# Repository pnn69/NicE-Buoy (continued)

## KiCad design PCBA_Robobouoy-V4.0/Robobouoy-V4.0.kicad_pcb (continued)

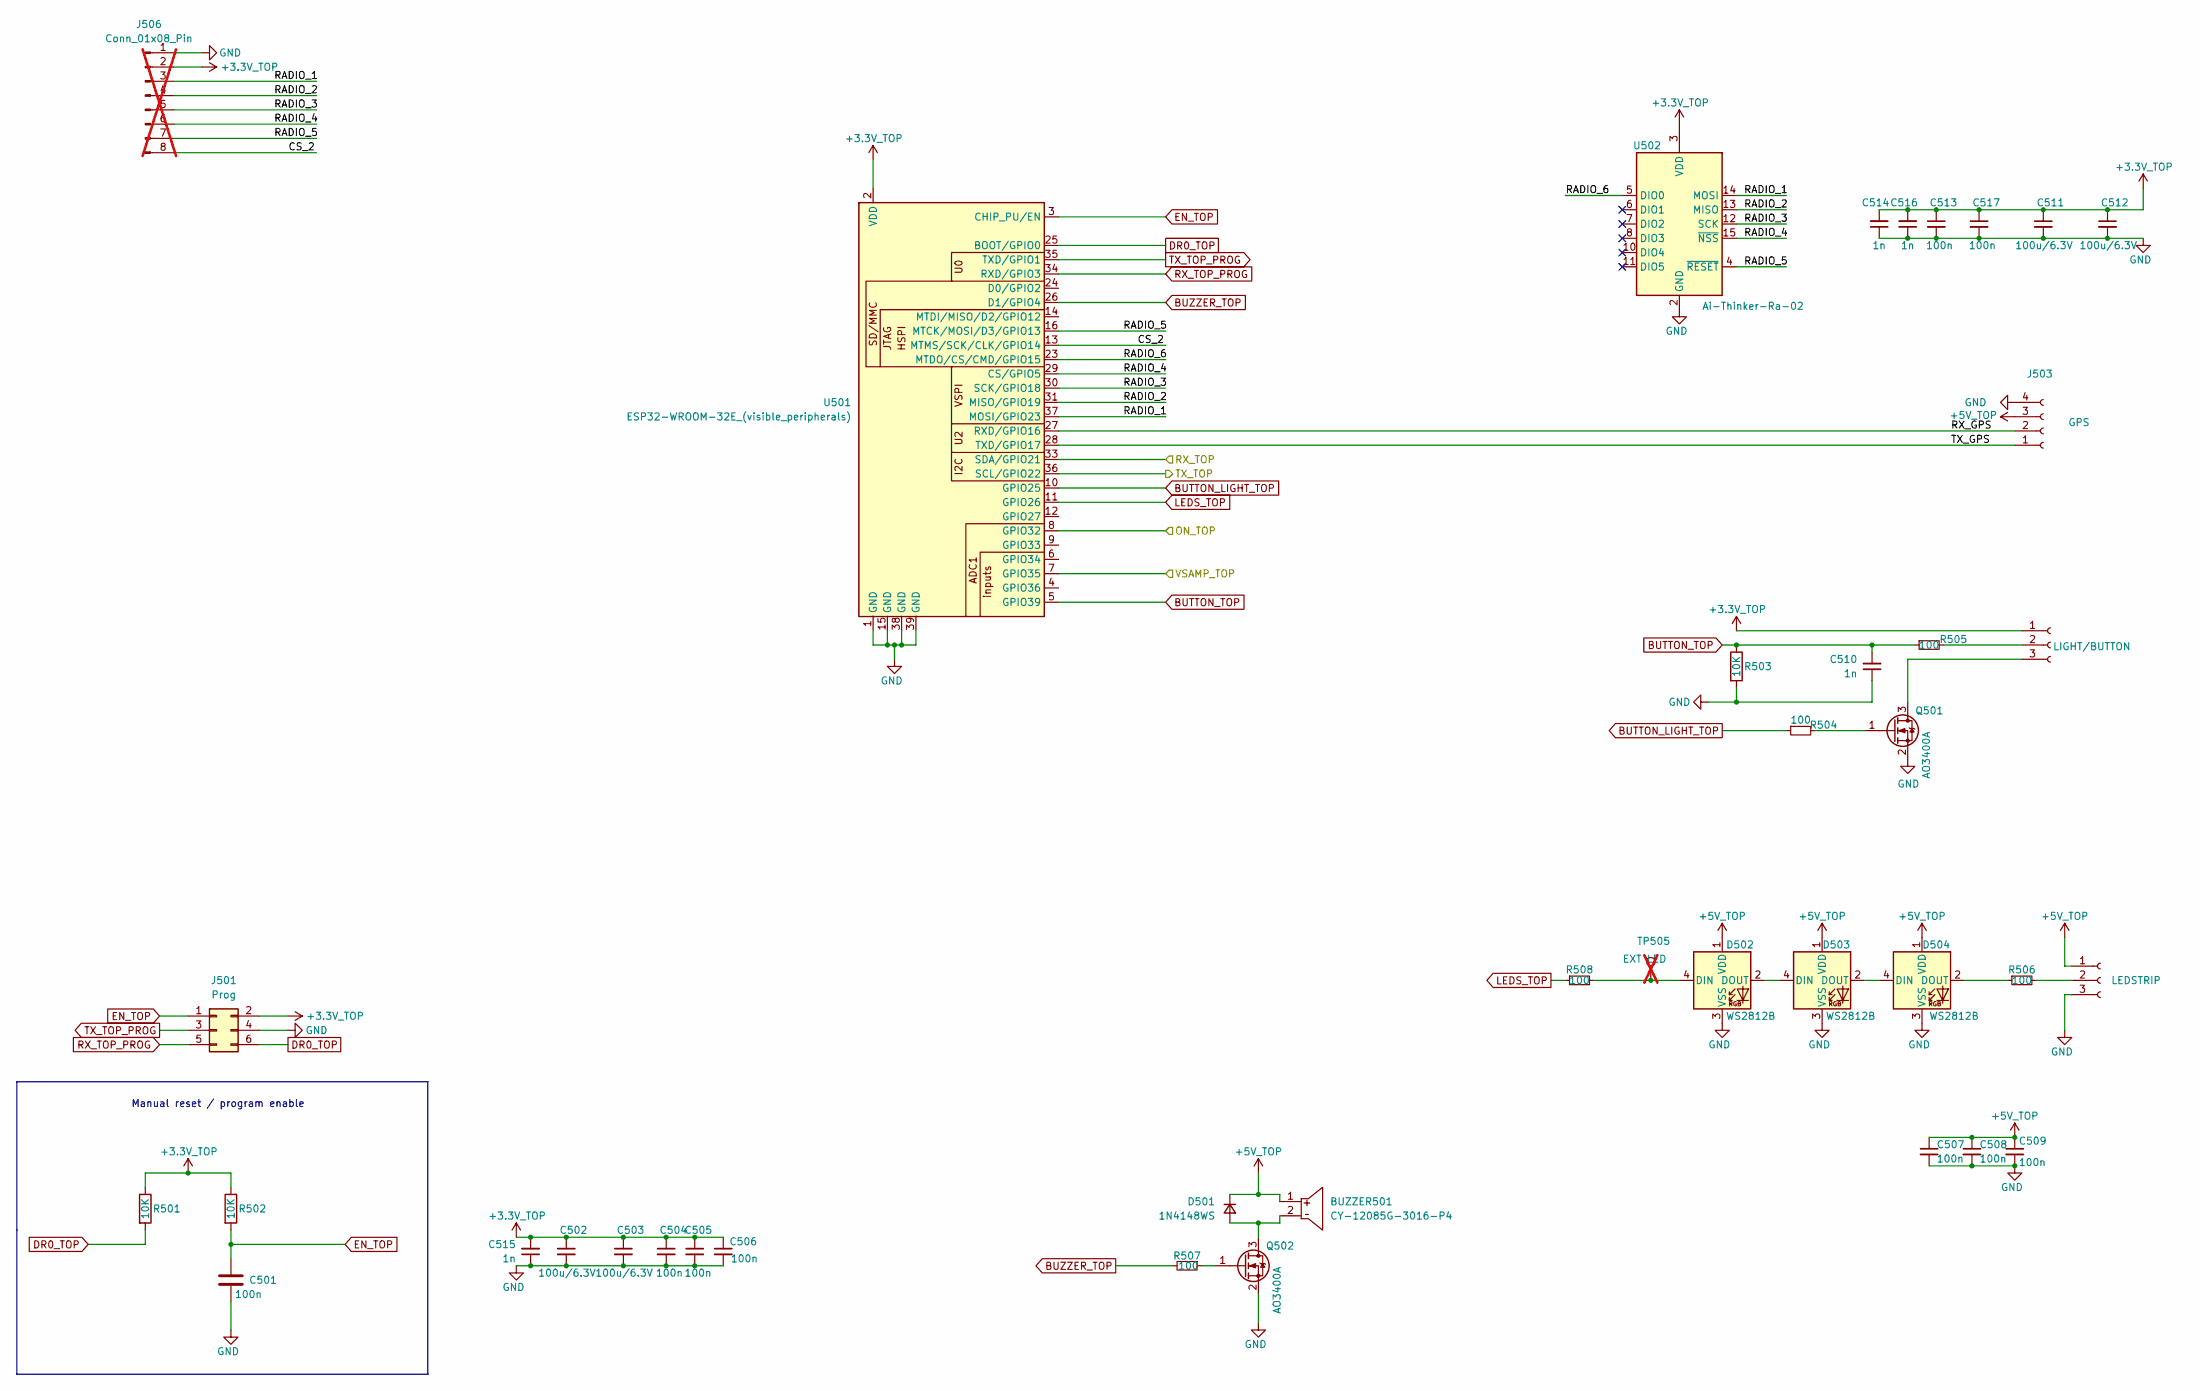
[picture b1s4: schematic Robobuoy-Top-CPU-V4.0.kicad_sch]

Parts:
BUZZER501: CY-12085G-3016-P4; BUZ-TH_BD12.0-P6.50-D0.6-FD; MPN Cy-12085G-3016-P4; LCSC Part C968749
C501, C504, C505, C506, C507, C508, C509, C513, C517: 100n; C_0603; LCSC C14663
C502, C503, C511, C512: 100u/6.3V; C_1206_3216Metric; LCSC C16133
C510, C514, C515, C516: 1n; C_0603; LCSC C1588
D501: 1N4148WS; D_SOD-323_1.8x1.4x1.15; LCSC C2128
D502, D503, D504: WS2812B; LED_WS2812B_PLCC4_5.0x5.0mm_P3.2mm; LCSC C2843785
J501: Prog; IDC_2x3_1.27mm; LCSC C42372545
J502: LIGHT/BUTTON; JST_XH_B3B-XH-A_1x03_P2.50mm_Vertical; LCSC C5341202
J503: GPS; JST_XH_B4B-XH-A_1x04_P2.50mm_Vertical; LCSC C5341203
J504: LEDSTRIP; JST_XH_B3B-XH-A_1x03_P2.50mm_Vertical; LCSC C5341202
J506: Conn_01x08_Pin; PinHeader_1x08_P2.54mm_Vertical_SMD_Pin1Left; not fitted
Q501, Q502: AO3400A; SOT-23; LCSC C20917
R501, R502, R503: 10K; R_0603; Farnell 2331736
R504, R505, R506, R507, R508: 100; R_0603; LCSC C22775
TP505: EXT LED; Testpoint_0.9x1.5; not fitted
U501: ESP32-WROOM-32E_(visible_peripherals); ESP32-WROOM-32; LCSC C82899
U502: Ai-Thinker-Ra-02; Ai-Thinker-Ra-02-LoRa; LCSC C90039

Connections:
+3.3V_TOP: C502.1, C503.1, C504.1, C505.1, C506.1, C511.1, C512.1, C513.1, C514.2, C515.2, C516.2, C517.1, J501.2, J502.1, J506.2, R501.1, R502.1, U501.2 (VDD), U502.3 (VDD); also elsewhere on the board
+5V_TOP: BUZZER501.1, C507.1, C508.1, C509.1, D501.1 (K), D502.1 (VDD), D503.1 (VDD), D504.1 (VDD), J503.3, J504.1; also elsewhere on the board
/Top-CPU-V4.0/CS_2: J506.8, U501.13 (MTMS/SCK/CLK/GPIO14)
/Top-CPU-V4.0/ON_TOP: U501.8 (GPIO32); also elsewhere on the board
/Top-CPU-V4.0/RADIO_1: J506.3, U501.37 (MOSI/GPIO23), U502.14 (MOSI)
/Top-CPU-V4.0/RADIO_2: J506.4, U501.31 (MISO/GPIO19), U502.13 (MISO)
/Top-CPU-V4.0/RADIO_3: J506.5, U501.30 (SCK/GPIO18), U502.12 (SCK)
/Top-CPU-V4.0/RADIO_4: J506.6, U501.29 (CS/GPIO5), U502.15 (~NSS)
/Top-CPU-V4.0/RADIO_5: J506.7, U501.16 (MTCK/MOSI/D3/GPIO13), U502.4 (~RESET)
/Top-CPU-V4.0/RADIO_6: U501.23 (MTDO/CS/CMD/GPIO15), U502.5 (DIO0)
/Top-CPU-V4.0/RX_GPS: J503.2, U501.27 (RXD/GPIO16)
/Top-CPU-V4.0/RX_TOP: U501.33 (SDA/GPIO21); also elsewhere on the board
/Top-CPU-V4.0/TX_GPS: J503.1, U501.28 (TXD/GPIO17)
/Top-CPU-V4.0/TX_TOP: U501.36 (SCL/GPIO22); also elsewhere on the board
/Top-CPU-V4.0/VSAMP_TOP: U501.7 (GPIO35); also elsewhere on the board
BUTTON_LIGHT_TOP: R504.1, U501.10 (GPIO25)
BUTTON_TOP: C510.2, R503.1, R505.1, U501.5 (GPIO39)
BUZZER_TOP: R507.2, U501.26 (D1/GPIO4)
DR0_TOP: J501.6, R501.2, U501.25 (BOOT/GPIO0)
EN_TOP: C501.1, J501.1, R502.2, U501.3 (CHIP_PU/EN)
GND: C501.2, C502.2, C503.2, C504.2, C505.2, C506.2, C507.2, C508.2, C509.2, C510.1, C511.2, C512.2, C513.2, C514.1, C515.1, C516.1, C517.2, D502.3 (VSS), D503.3 (VSS), D504.3 (VSS), J501.4, J503.4, J504.3, J506.1, Q501.2 (S), Q502.2 (S), R503.2, U501.1 (GND), U501.15 (GND), U501.38 (GND), U501.39 (GND), U502.1 (GND), U502.2 (GND), U502.9 (GND), U502.16 (GND); also elsewhere on the board
LEDS_TOP: R508.1, U501.11 (GPIO26)
unnamed: BUZZER501.2, D501.2 (A), Q502.3 (D)
unnamed: D502.4 (DIN), R508.2, TP505.1 (1_1)
unnamed: D502.2 (DOUT), D503.4 (DIN)
unnamed: D503.2 (DOUT), D504.4 (DIN)
unnamed: D504.2 (DOUT), R506.1
unnamed: J502.2, R505.2
unnamed: J502.3, Q501.3 (D)
unnamed: J504.2, R506.2
unnamed: Q501.1 (G), R504.2
unnamed: Q502.1 (G), R507.1
RX_TOP_PROG: J501.5, U501.34 (RXD/GPIO3)
TX_TOP_PROG: J501.3, U501.35 (TXD/GPIO1)

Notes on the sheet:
Manual reset / program enable

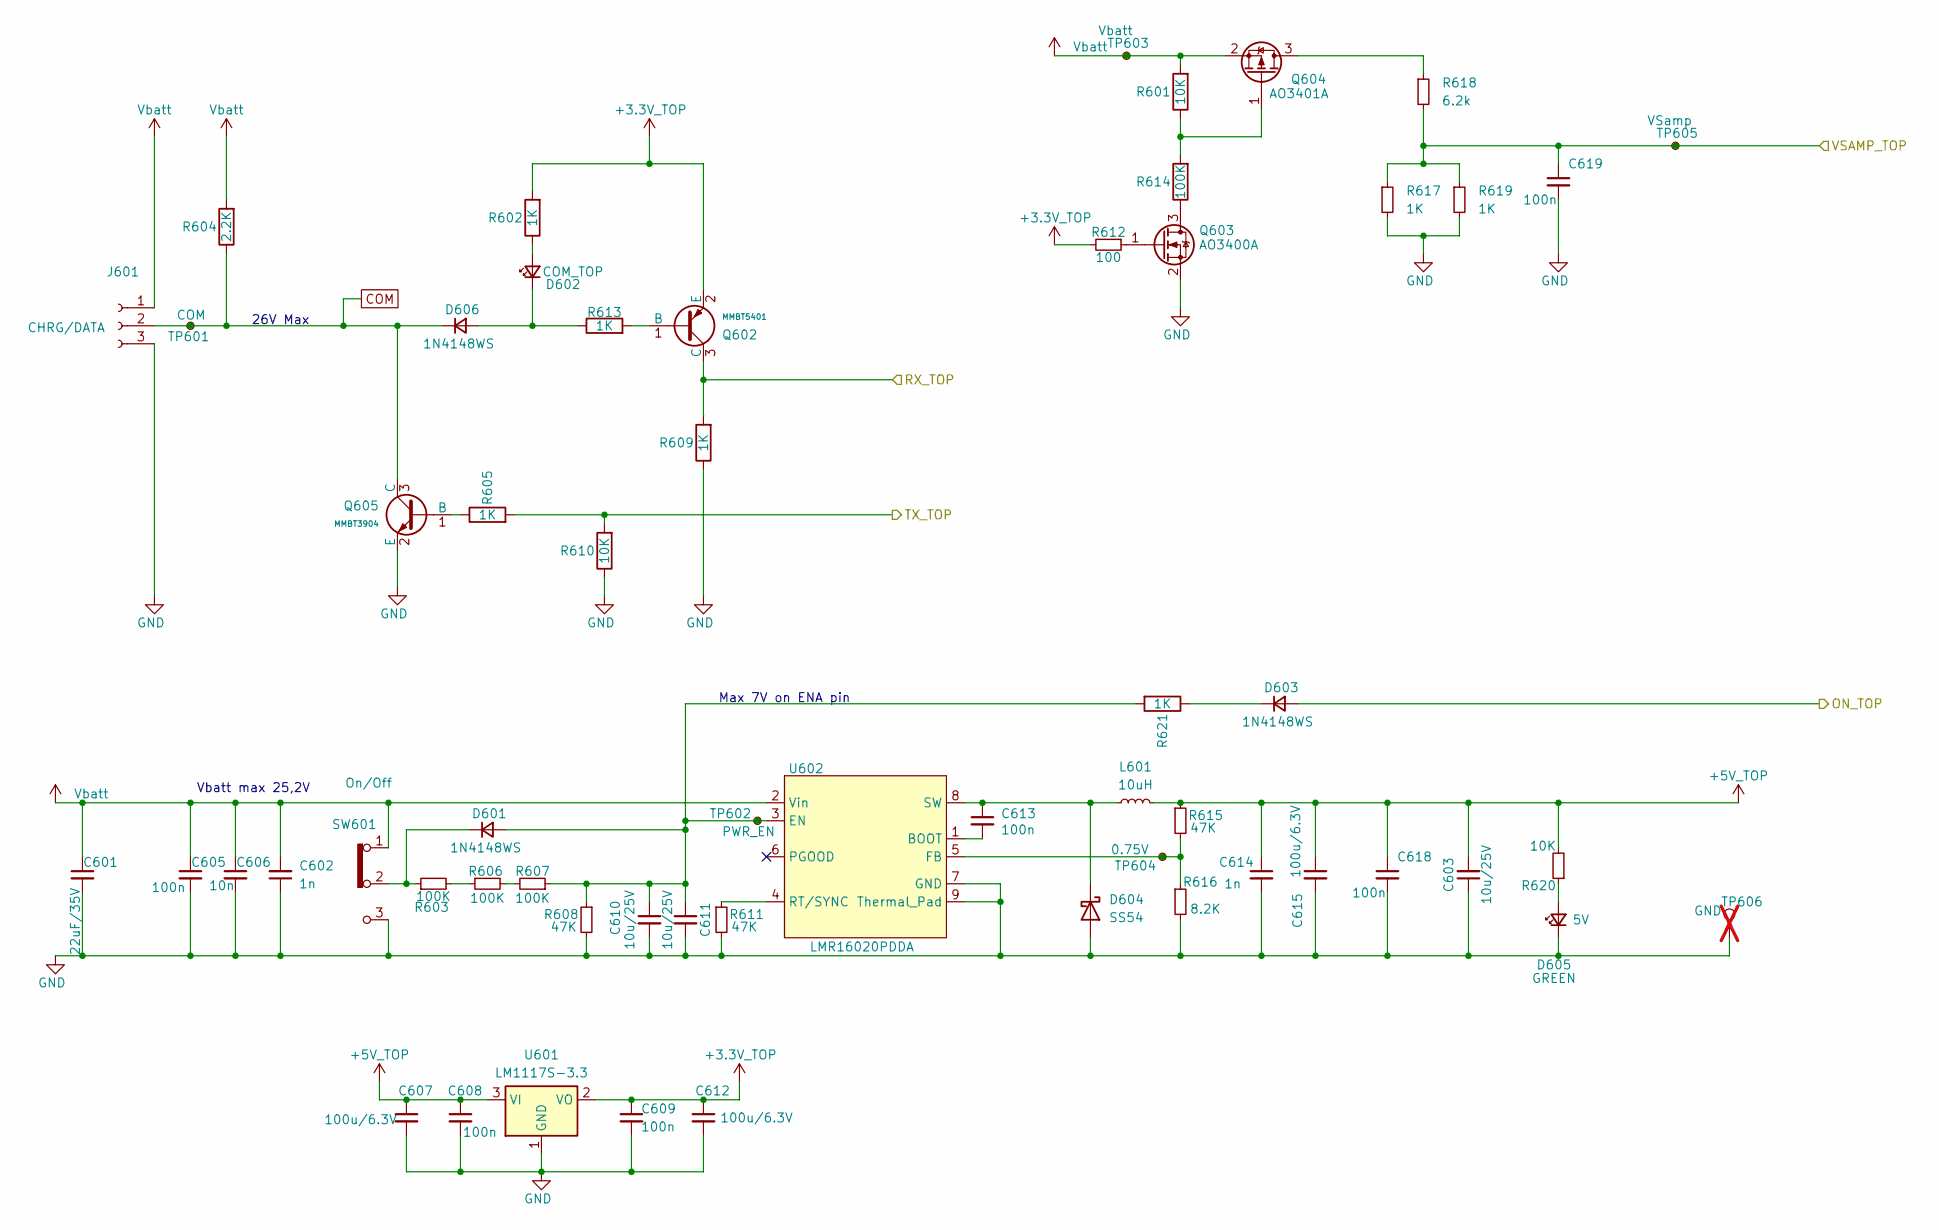
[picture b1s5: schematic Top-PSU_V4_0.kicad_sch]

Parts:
C601: 22uF/35V; C_1206_3216Metric; LCSC C6119969
C602, C614: 1n; C_0603; LCSC C1588
C603, C610, C611: 10u/25V; C_0805; LCSC C15850
C605, C608, C609, C613, C618, C619: 100n; C_0603; LCSC C14663
C606: 10n; C_0603; LCSC C57112
C607, C612, C615: 100u/6.3V; C_1206_3216Metric; LCSC C16133
D601, D603, D606: 1N4148WS; D_SOD-323_1.8x1.4x1.15; LCSC C2128
D602: COM_TOP; LED_0603; LCSC C2286
D604: SS54; D_SMA; LCSC C22452
D605: GREEN; LED_0603_1608Metric; LCSC C2286
J601: CHRG/DATA; JST_XH_B3B-XH-A_1x03_P2.50mm_Vertical; LCSC C5341202
L601: 10uH; L_6.6x7.0mm; LCSC C2894722
Q602: MMBT5401; Q_SOT-23; Part MMBT5401; LCSC C7420356
Q603: AO3400A; SOT-23; LCSC C20917
Q604: AO3401A; SOT-23; LCSC C15127
Q605: MMBT3904; Q_SOT-23; Part MMBT3904; LCSC C7420353
R601, R610: 10K; R_0603; Farnell 2331736
R602, R605, R609, R613, R617, R619, R621: 1K; R_0603; LCSC C21190
R603, R606, R607: 100K; R_0603; LCSC C25803
R604: 2.2K; R_0603; LCSC C4190
R608, R611, R615: 47K; R_0603; LCSC C25819
R612: 100; R_0603; LCSC C22775
R614: 100K; R_0603; Farnell 2331736
R616: 8.2K; R_0603; LCSC C25981
R618: 6.2k; R_0603; LCSC C4260
R620: 10K; R_0603; LCSC C25804
SW601: On/Off; Header_1x03_P2.54_Male; LCSC C2937625
TP601: COM; Testpad_1
TP602: PWR_EN; Testpad_1
TP603: Vbatt; Testpad_1
TP604: 0.75V; Testpad_1
TP605: VSamp; Testpad_1
TP606: GND; Testpoint_0.9x1.5; not fitted
U601: LM1117S-3.3; SOT223; LCSC C6186
U602: LMR16020PDDA; SOIC-8-1EP_3.9x4.9mm_P1.27mm_EP2.41x3.81mm_ThermalVias; LCSC C190006

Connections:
+3.3V_TOP: C609.1, C612.1, Q602.2 (E), R602.2, R612.2, U601.2 (VO); also elsewhere on the board
+5V_TOP: C603.2, C607.1, C608.1, C614.1, C615.1, C618.1, L601.2, R615.1, R620.2, U601.3 (VI); also elsewhere on the board
/Top-CPU-V4.0/ON_TOP: D603.2 (A); also elsewhere on the board
/Top-CPU-V4.0/RX_TOP: Q602.3 (C), R609.2; also elsewhere on the board
/Top-CPU-V4.0/TX_TOP: R605.2, R610.2; also elsewhere on the board
/Top-CPU-V4.0/VSAMP_TOP: C619.1, R617.1, R618.2, R619.1, TP605.1 (1_1); also elsewhere on the board
COM: D606.1 (K), J601.2, Q605.3 (C), R604.1, TP601.1 (1_1); also elsewhere on the board
GND: C601.2, C602.1, C603.1, C605.2, C606.2, C607.2, C608.2, C609.2, C610.2, C611.2, C612.2, C614.2, C615.2, C618.2, C619.2, D604.2 (A), D605.1 (K), J601.3, Q603.2 (S), Q605.2 (E), R608.2, R609.1, R610.1, R611.2, R616.2, R617.2, R619.2, SW601.3, TP606.1 (1_1), U601.1 (GND), U602.7 (GND), U602.9 (Thermal_Pad); also elsewhere on the board
unnamed: C610.1, C611.1, D601.2 (A), R607.1, R608.1, R621.2, TP602.1 (1_1), U602.3 (EN)
unnamed: D601.1 (K), R603.1, SW601.2
unnamed: D602.2 (A), R602.1
unnamed: D602.1 (K), D606.2 (A), R613.1
unnamed: D603.1 (K), R621.1
unnamed: C613.1, D604.1 (K), L601.1, U602.8 (SW)
unnamed: D605.2 (A), R620.1
unnamed: Q602.1 (B), R613.2
unnamed: Q603.3 (D), R614.1
unnamed: Q603.1 (G), R612.1
unnamed: Q604.3 (D), R618.1
unnamed: Q604.1 (G), R601.1, R614.2
unnamed: Q605.1 (B), R605.1
unnamed: R603.2, R606.1
unnamed: R606.2, R607.2
unnamed: C613.2, U602.1 (BOOT)
unnamed: R615.2, R616.1, TP604.1 (1_1), U602.5 (FB)
unnamed: R611.1, U602.4 (RT/SYNC)
Vbatt: C601.1, C602.2, C605.1, C606.1, J601.1, Q604.2 (S), R601.2, R604.2, SW601.1, TP603.1 (1_1), U602.2 (Vin); also elsewhere on the board

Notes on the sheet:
Vbatt max 25,2V
Max 7V on ENA pin
26V Max

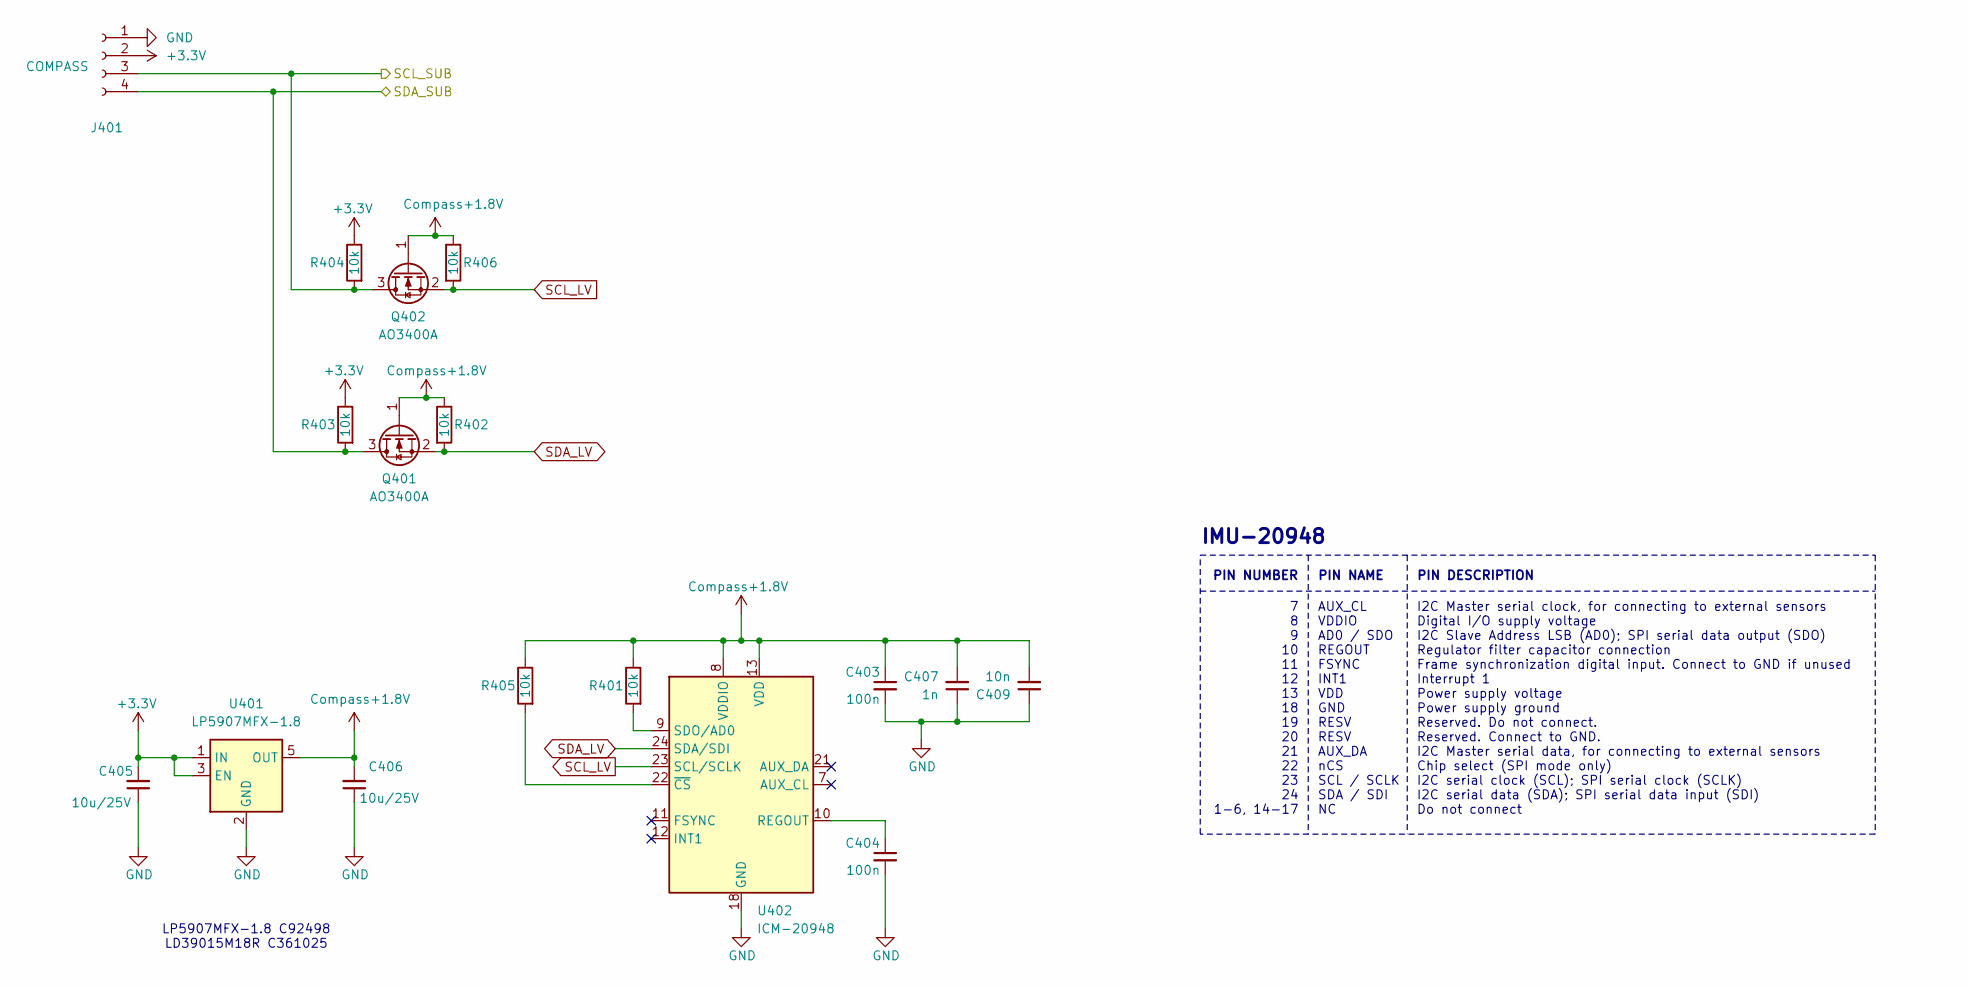
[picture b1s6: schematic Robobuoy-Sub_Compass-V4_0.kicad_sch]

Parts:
C403, C404: 100n; C_0402; LCSC C1525
C405, C406: 10u/25V; C_0805; LCSC C15850
C407: 1n; C_0402; LCSC C1523
C409: 10n; C_0402; LCSC C15195
J401: COMPASS; JST_XH_B4B-XH-A_1x04_P2.50mm_Vertical; LCSC C5341203
Q401, Q402: AO3400A; SOT-23; LCSC C20917
R401, R402, R403, R404, R405, R406: 10k; R_0402; Farnell 2331736
U401: LP5907MFX-1.8; SOT-23-5
U402: ICM-20948; QFN-24_L3.0-W3.0-P0.40-BL-EP

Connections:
+3.3V: C405.2, J401.2, R403.1, R404.1, U401.1 (IN), U401.3 (EN); also elsewhere on the board
/Suv-CPU-V4.0/SCL_SUB: J401.3, Q402.3 (D), R404.2; also elsewhere on the board
/Suv-CPU-V4.0/SDA_SUB: J401.4, Q401.3 (D), R403.2; also elsewhere on the board
Compass+1.8V: C403.1, C406.2, C407.2, C409.2, Q401.1 (G), Q402.1 (G), R401.1, R402.1, R405.1, R406.1, U401.5 (OUT), U402.8 (VDDIO), U402.13 (VDD)
GND: C403.2, C404.2, C405.1, C406.1, C407.1, C409.1, J401.1, U401.2 (GND), U402.18 (GND), U402.20 (GND); also elsewhere on the board
unnamed: C404.1, U402.10 (REGOUT)
unnamed: R401.2, U402.9 (SDO/AD0)
unnamed: R405.2, U402.22 (~CS)
SCL_LV: Q402.2 (S), R406.2, U402.23 (SCL/SCLK)
SDA_LV: Q401.2 (S), R402.2, U402.24 (SDA/SDI)

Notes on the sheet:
PIN NAME
LP5907MFX-1.8 C92498 LD39015M18R C361025
7 8 9 10 11 12 13 18 19 20 21 22 23 24 1-6, 14-17
IMU-20948
PIN NUMBER
PIN DESCRIPTION
I2C Master serial clock, for connecting to external sensors Digital I/O supply voltage I2C Slave Address LSB (AD0); SPI serial data output (SDO) Regulator filter capacitor connection Frame synchronization digital input. Connect to GND if unused Interrupt 1 Power supply voltage Power supply ground R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
AUX_CL VDDIO AD0 / SDO REGOUT FSYNC INT1 VDD GND RESV RESV AUX_DA nCS SCL / SCLK SDA / SDI NC

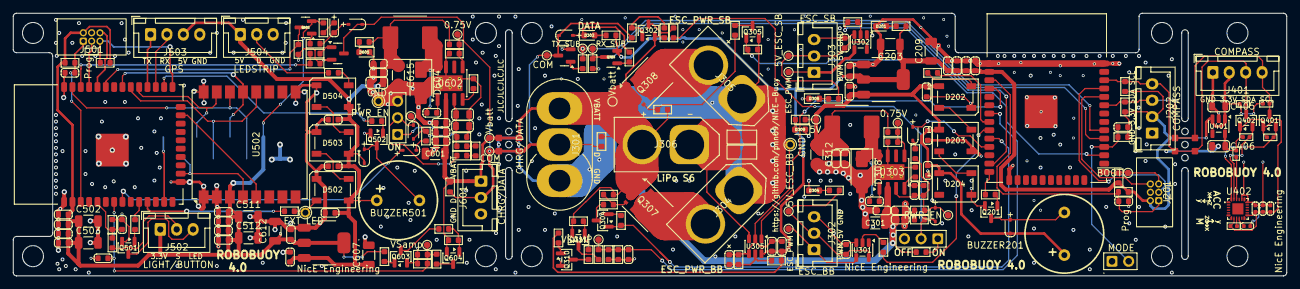
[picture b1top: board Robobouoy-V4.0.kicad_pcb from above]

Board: 4 copper layers, 194.0 x 40.0 mm, 258 parts (1 on the bottom side), 122 nets.

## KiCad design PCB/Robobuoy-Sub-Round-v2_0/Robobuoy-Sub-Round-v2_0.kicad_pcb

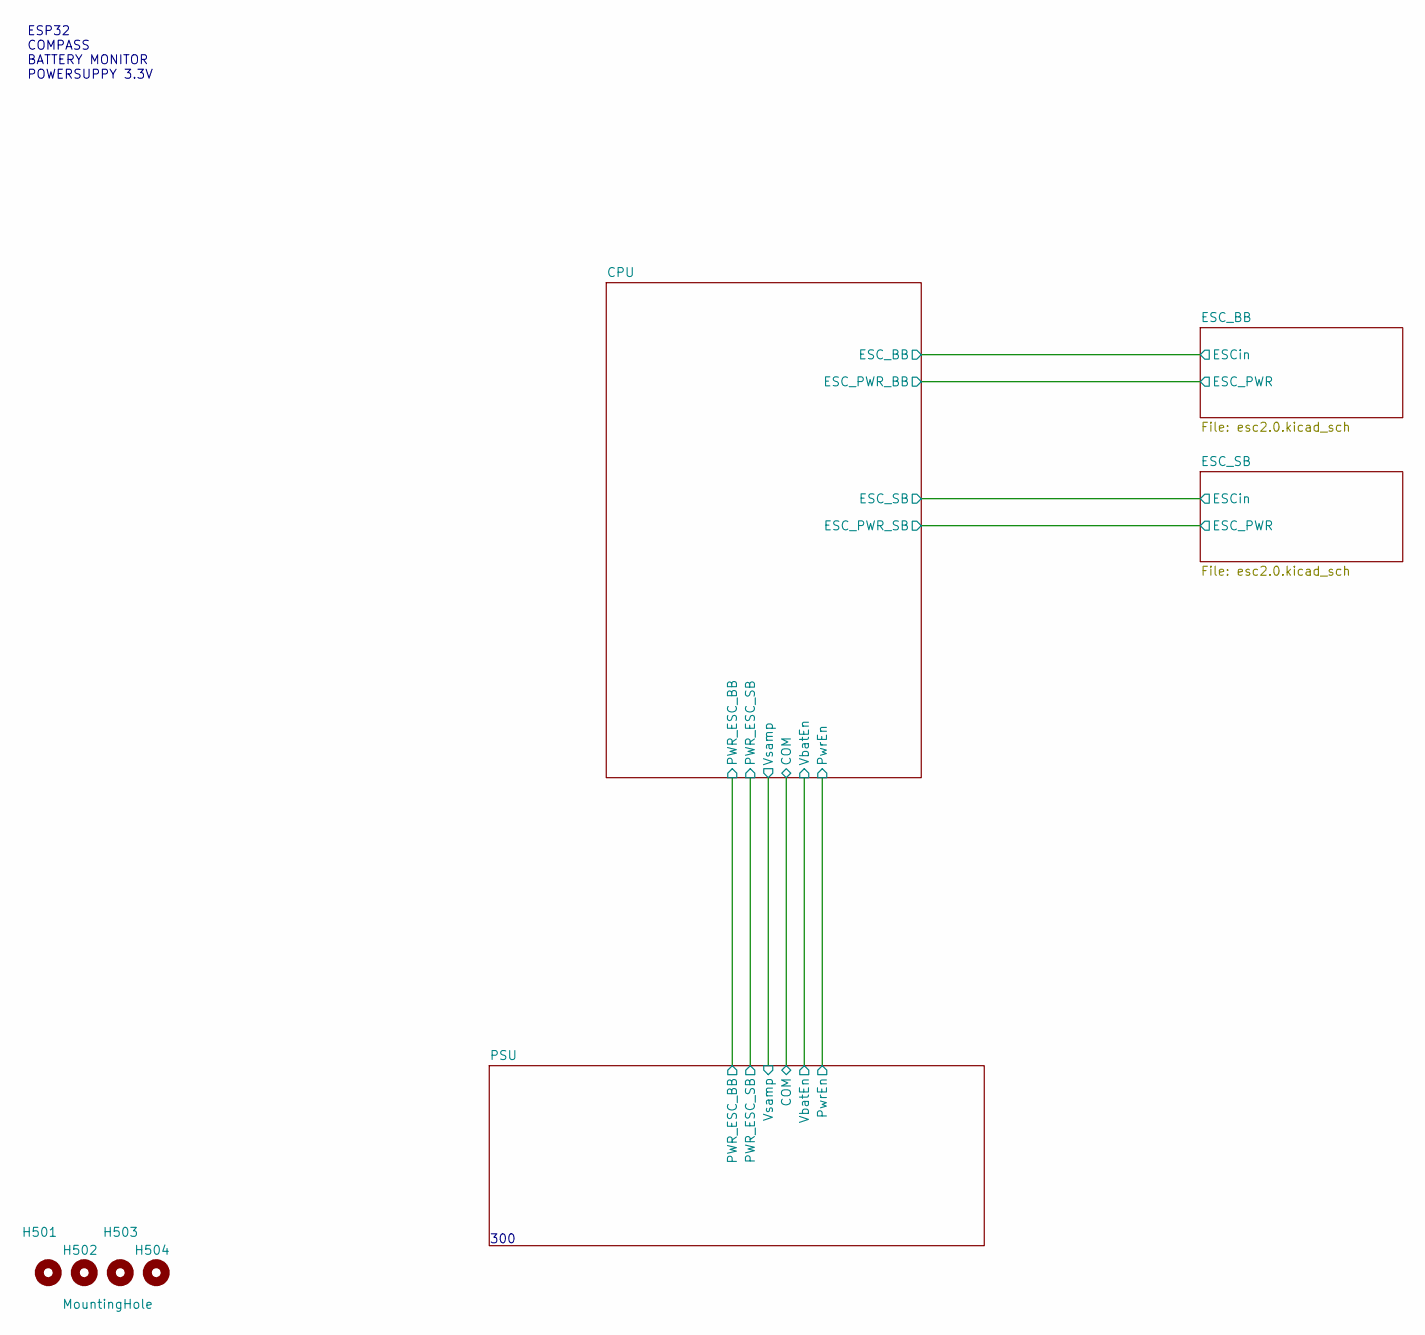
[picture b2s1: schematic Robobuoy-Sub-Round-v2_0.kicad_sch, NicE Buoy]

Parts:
H501, H502, H503, H504: MountingHole; NPTH_M3

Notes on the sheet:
300
ESP32 COMPASS BATTERY MONITOR POWERSUPPY 3.3V

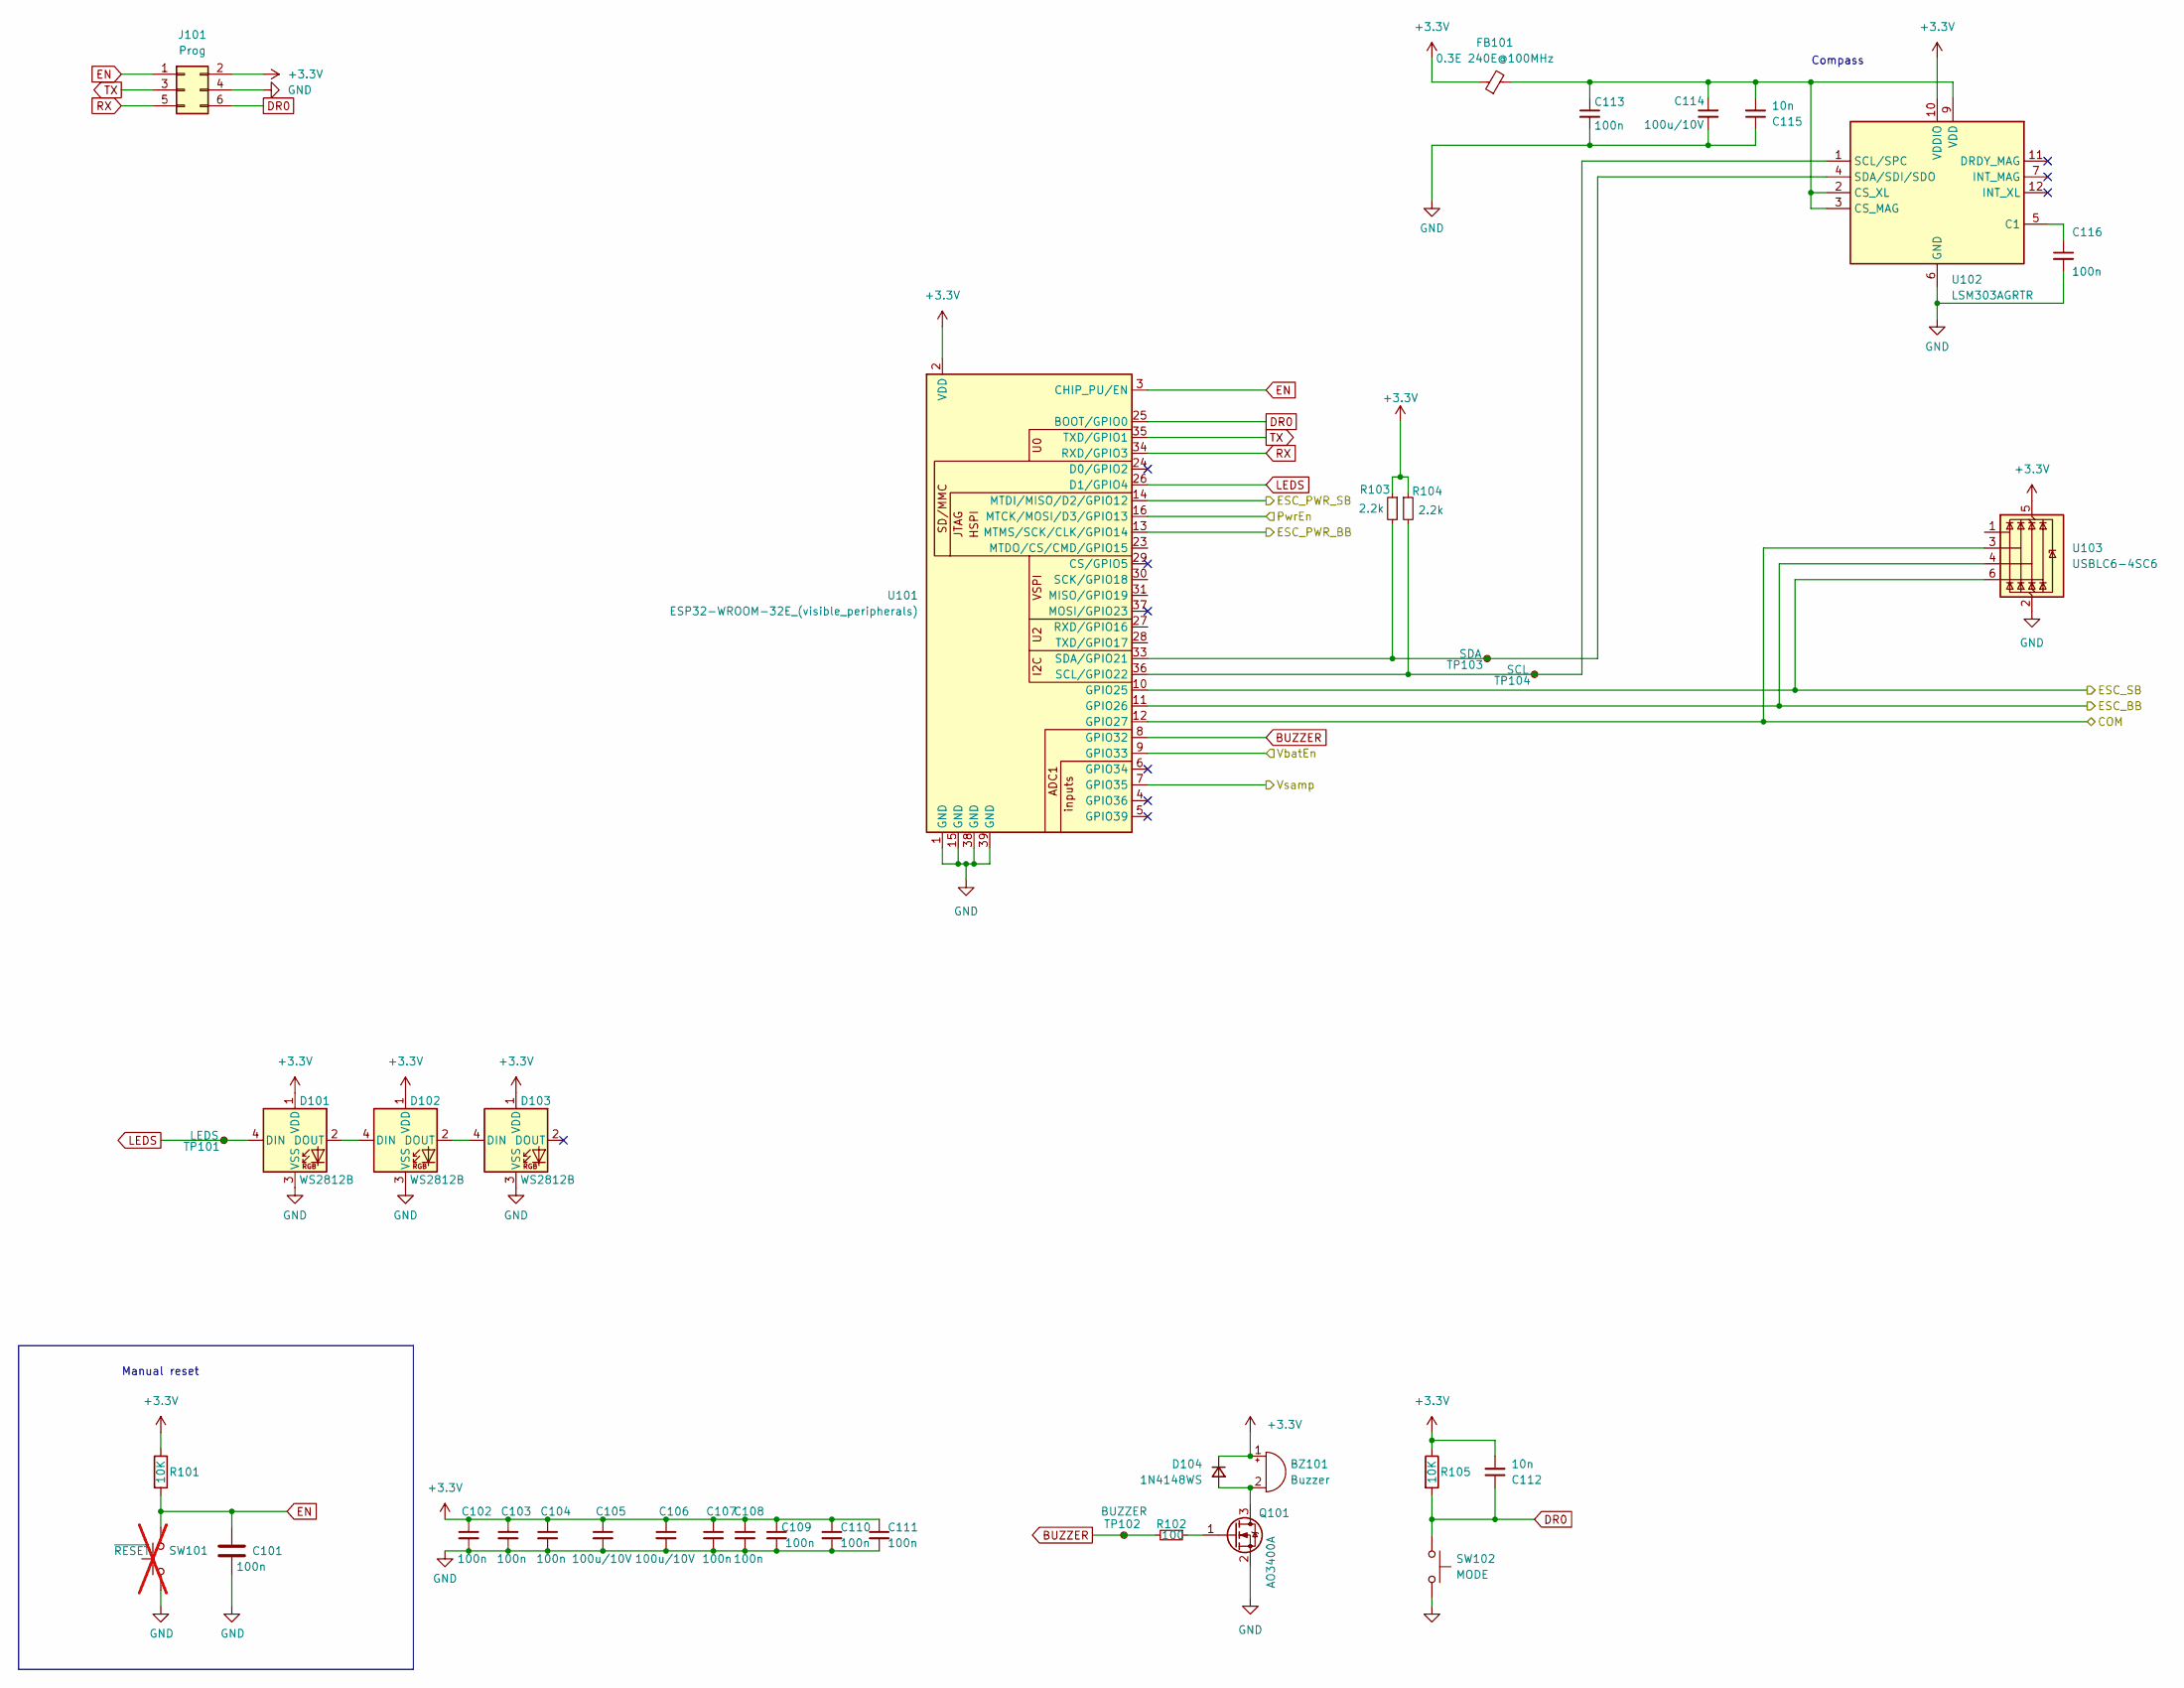
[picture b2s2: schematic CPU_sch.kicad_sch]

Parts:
BZ101: Buzzer; Buzzer-12x6.5x5.2; LCSC C968749
C101, C102, C103, C104, C107, C108, C109, C110, C111, C113, C116: 100n; C_0603; LCSC C14663
C105, C106, C114: 100u/10V; C_1210_3225Metric; LCSC C23742
C112, C115: 10n; C_0603; LCSC C57112
D101, D102, D103: WS2812B; LED_WS2812B_PLCC4_5.0x5.0mm_P3.2mm; LCSC C2843785
D104: 1N4148WS; D_SOD-323_1.8x1.4x1.15; LCSC C2128
FB101: 0.3E 240E@100MHz; L_0805_(1.2); LCSC C2941558
J101: Prog; IDC-Header_2x03_P2.54mm_Vertical; LCSC C65114
Q101: AO3400A; SOT-23; LCSC C20917
R101, R105: 10K; R_0603; Farnell 2331736
R102: 100; R_0603; LCSC C22775
R103, R104: 2.2k; R_0603; LCSC C4190
SW101: ~{RESET}; PinHeader_1x02_P2.54mm_Vertical; not fitted
SW102: MODE; SW_SPST_TL3342; LCSC C318884
TP101: LEDS; Testpad_1
TP102: BUZZER; Testpad_1
TP103: SDA; Testpad_1
TP104: SCL; Testpad_1
U101: ESP32-WROOM-32E_(visible_peripherals); ESP32-WROOM-32; LCSC C82899
U102: LSM303AGRTR; LGA-12_2x2mm_P0.5mm; LCSC C126671
U103: USBLC6-4SC6; SOT-23-6; LCSC C5197386

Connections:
+3.3V: BZ101.1 (+), C102.1, C103.1, C104.1, C105.1, C106.1, C107.1, C108.1, C109.1, C110.1, C111.1, C112.2, D101.1 (VDD), D102.1 (VDD), D103.1 (VDD), D104.1 (K), FB101.1, J101.2, R101.1, R103.1, R104.1, R105.1, U101.2 (VDD), U102.10 (VDDIO), U103.5 (VBUS); also elsewhere on the board
/CPU/COM: U101.12 (GPIO27), U103.3 (I/O2); also elsewhere on the board
/CPU/ESC_BB: U101.11 (GPIO26), U103.4 (I/O3); also elsewhere on the board
/CPU/ESC_PWR_BB: U101.13 (MTMS/SCK/CLK/GPIO14); also elsewhere on the board
/CPU/ESC_PWR_SB: U101.14 (MTDI/MISO/D2/GPIO12); also elsewhere on the board
/CPU/ESC_SB: U101.10 (GPIO25), U103.6 (I/O4); also elsewhere on the board
/CPU/PwrEn: U101.16 (MTCK/MOSI/D3/GPIO13); also elsewhere on the board
/CPU/VbatEn: U101.9 (GPIO33); also elsewhere on the board
/CPU/Vsamp: U101.7 (GPIO35); also elsewhere on the board
BUZZER: R102.2, TP102.1, U101.8 (GPIO32)
DR0: C112.1, J101.6, R105.2, SW102.2, U101.25 (BOOT/GPIO0)
EN: C101.1, J101.1, R101.2, SW101.2, U101.3 (CHIP_PU/EN)
GND: C101.2, C102.2, C103.2, C104.2, C105.2, C106.2, C107.2, C108.2, C109.2, C110.2, C111.2, C113.2, C114.2, C115.1, C116.2, D101.3 (VSS), D102.3 (VSS), D103.3 (VSS), J101.4, Q101.2 (S), SW101.1, SW102.1, U101.1 (GND), U101.15 (GND), U101.38 (GND), U101.39 (GND), U102.6 (GND), U102.8 (GND), U103.2 (GND); also elsewhere on the board
LEDS: D101.4 (DIN), TP101.1, U101.26 (D1/GPIO4)
unnamed: BZ101.2 (-), D104.2 (A), Q101.3 (D)
unnamed: D101.2 (DOUT), D102.4 (DIN)
unnamed: D102.2 (DOUT), D103.4 (DIN)
unnamed: Q101.1 (G), R102.1
unnamed: R104.2, TP104.1, U101.36 (SCL/GPIO22), U102.1 (SCL/SPC)
unnamed: R103.2, TP103.1, U101.33 (SDA/GPIO21), U102.4 (SDA/SDI/SDO)
unnamed: C116.1, U102.5 (C1)
unnamed: C113.1, C114.1, C115.2, FB101.2, U102.2 (CS_XL), U102.3 (CS_MAG), U102.9 (VDD)
RX: J101.5, U101.34 (RXD/GPIO3)
TX: J101.3, U101.35 (TXD/GPIO1)

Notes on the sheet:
Compass
Manual reset

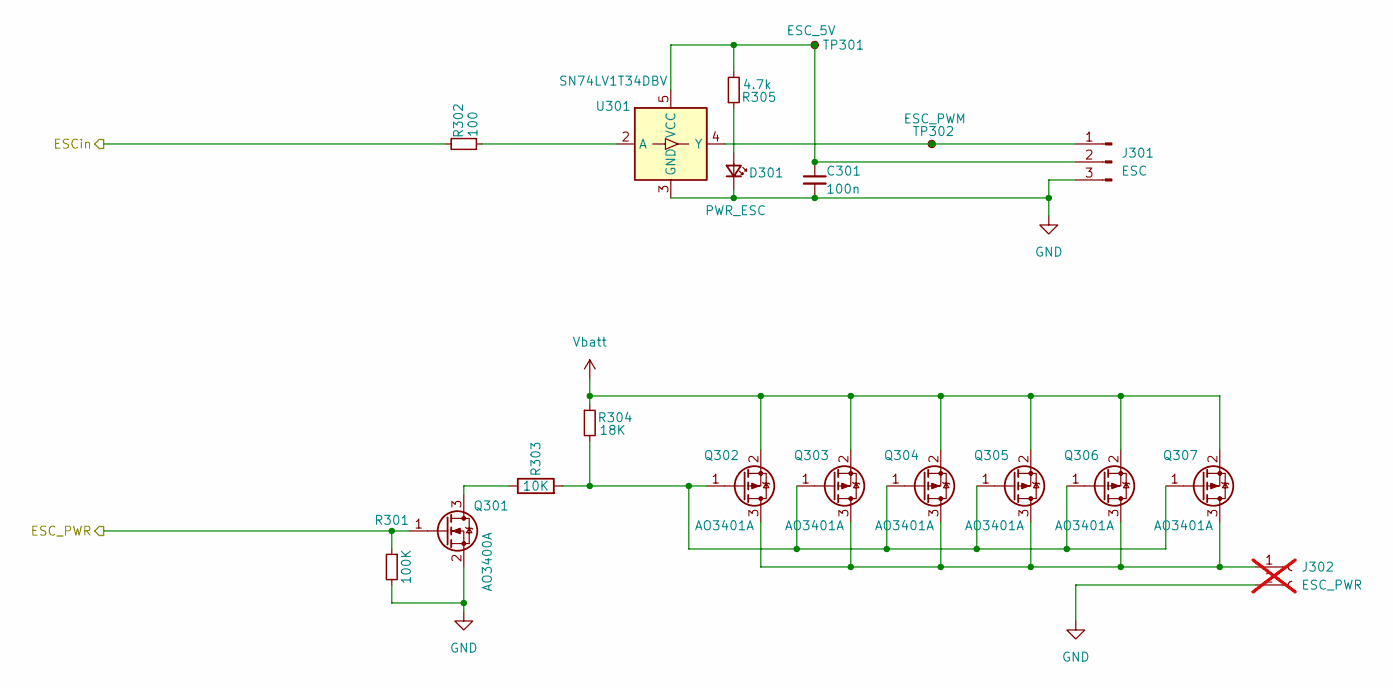
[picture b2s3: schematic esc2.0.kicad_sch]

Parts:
C301: 100n; C_0603; LCSC C14663
D301: PWR_ESC; LED_0603_1608Metric; LCSC C2286
J301: ESC; JST_XH_B3B-XH-A_1x03_P2.50mm_Vertical; LCSC C5341202
J302: ESC_PWR; SolderWire-0.75sqmm_1x02_P4.8mm_D1.25mm_OD2.3mm; not fitted
Q301: AO3400A; SOT-23; LCSC C20917
Q302, Q303, Q304, Q305, Q306, Q307: AO3401A; SOT-23; LCSC C15127
R301: 100K; R_0603; LCSC C25804
R302: 100; R_0603; LCSC C22775
R303: 10K; R_0603; Farnell 2331736
R304: 18K; R_0603; LCSC C25810
R305: 4.7k; R_0603; LCSC C4177
TP301: ESC_5V; Testpad_1
TP302: ESC_PWM; Testpad_1
U301: SN74LV1T34DBV; SOT-23-5; LCSC C100024

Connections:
/CPU/ESC_PWR_SB: Q301.1 (G), R301.1; also elsewhere on the board
/CPU/ESC_SB: R302.2; also elsewhere on the board
GND: C301.2, D301.1 (K), J301.3, J302.2, Q301.2 (S), R301.2, U301.3 (GND); also elsewhere on the board
unnamed: D301.2 (A), R305.1
unnamed: J301.1, TP302.1, U301.4 (Y)
unnamed: C301.1, J301.2, R305.2, TP301.1, U301.5 (VCC)
unnamed: J302.1, Q302.3 (D), Q303.3 (D), Q304.3 (D), Q305.3 (D), Q306.3 (D), Q307.3 (D)
unnamed: Q301.3 (D), R303.1
unnamed: Q302.1 (G), Q303.1 (G), Q304.1 (G), Q305.1 (G), Q306.1 (G), Q307.1 (G), R303.2, R304.2
unnamed: R302.1, U301.2 (A)
Vbatt: Q302.2 (S), Q303.2 (S), Q304.2 (S), Q305.2 (S), Q306.2 (S), Q307.2 (S), R304.1; also elsewhere on the board

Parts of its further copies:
C401: 100n; C_0603; LCSC C14663
D401: PWR_ESC; LED_0603_1608Metric; LCSC C2286
J401: ESC; JST_XH_B3B-XH-A_1x03_P2.50mm_Vertical; LCSC C5341202
J402: ESC_PWR; SolderWire-0.75sqmm_1x02_P4.8mm_D1.25mm_OD2.3mm; not fitted
Q401: AO3400A; SOT-23; LCSC C20917
Q402, Q403, Q404, Q405, Q406, Q407: AO3401A; SOT-23; LCSC C15127
R401: 100K; R_0603; LCSC C25804
R402: 100; R_0603; LCSC C22775
R403: 10K; R_0603; Farnell 2331736
R404: 18K; R_0603; LCSC C25810
R405: 4.7k; R_0603; LCSC C4177
TP401: ESC_5V; Testpad_1
TP402: ESC_PWM; Testpad_1
U401: SN74LV1T34DBV; SOT-23-5; LCSC C100024

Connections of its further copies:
/CPU/ESC_BB: R402.2; also elsewhere on the board
/CPU/ESC_PWR_BB: Q401.1 (G), R401.1; also elsewhere on the board
GND: C401.2, D401.1 (K), J401.3, J402.2, Q401.2 (S), R401.2, U401.3 (GND); also elsewhere on the board
unnamed: D401.2 (A), R405.1
unnamed: J401.1, TP402.1, U401.4 (Y)
unnamed: C401.1, J401.2, R405.2, TP401.1, U401.5 (VCC)
unnamed: J402.1, Q402.3 (D), Q403.3 (D), Q404.3 (D), Q405.3 (D), Q406.3 (D), Q407.3 (D)
unnamed: Q401.3 (D), R403.1
unnamed: Q402.1 (G), Q403.1 (G), Q404.1 (G), Q405.1 (G), Q406.1 (G), Q407.1 (G), R403.2, R404.2
unnamed: R402.1, U401.2 (A)
Vbatt: Q402.2 (S), Q403.2 (S), Q404.2 (S), Q405.2 (S), Q406.2 (S), Q407.2 (S), R404.1; also elsewhere on the board
